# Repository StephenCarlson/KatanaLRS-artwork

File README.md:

KatanaLRS-artwork
=================

Hardware Files: Schematics and Layouts, Gerbers, PDFs

License
-------

This work is licensed under the Creative Commons Attribution-ShareAlike 3.0 Unported License. To view a copy of this license, visit <http://creativecommons.org/licenses/by-sa/3.0/> or send a letter to Creative Commons, 444 Castro Street, Suite 900, Mountain View, California, 94041, USA.

*Some portions of code may be subject to different licensing agreements.

THE SOFTWARE IS PROVIDED “AS IS”, WITHOUT WARRANTY OF ANY KIND, EXPRESS OR IMPLIED, INCLUDING BUT NOT LIMITED TO THE WARRANTIES OF MERCHANTABILITY, FITNESS FOR A PARTICULAR PURPOSE AND NONINFRINGEMENT. IN NO EVENT SHALL THE AUTHORS OR COPYRIGHT HOLDERS BE LIABLE FOR ANY CLAIM, DAMAGES OR OTHER LIABILITY, WHETHER IN AN ACTION OF CONTRACT, TORT OR OTHERWISE, ARISING FROM, OUT OF OR IN CONNECTION WITH THE SOFTWARE OR THE USE OR OTHER DEALINGS IN THE SOFTWARE.

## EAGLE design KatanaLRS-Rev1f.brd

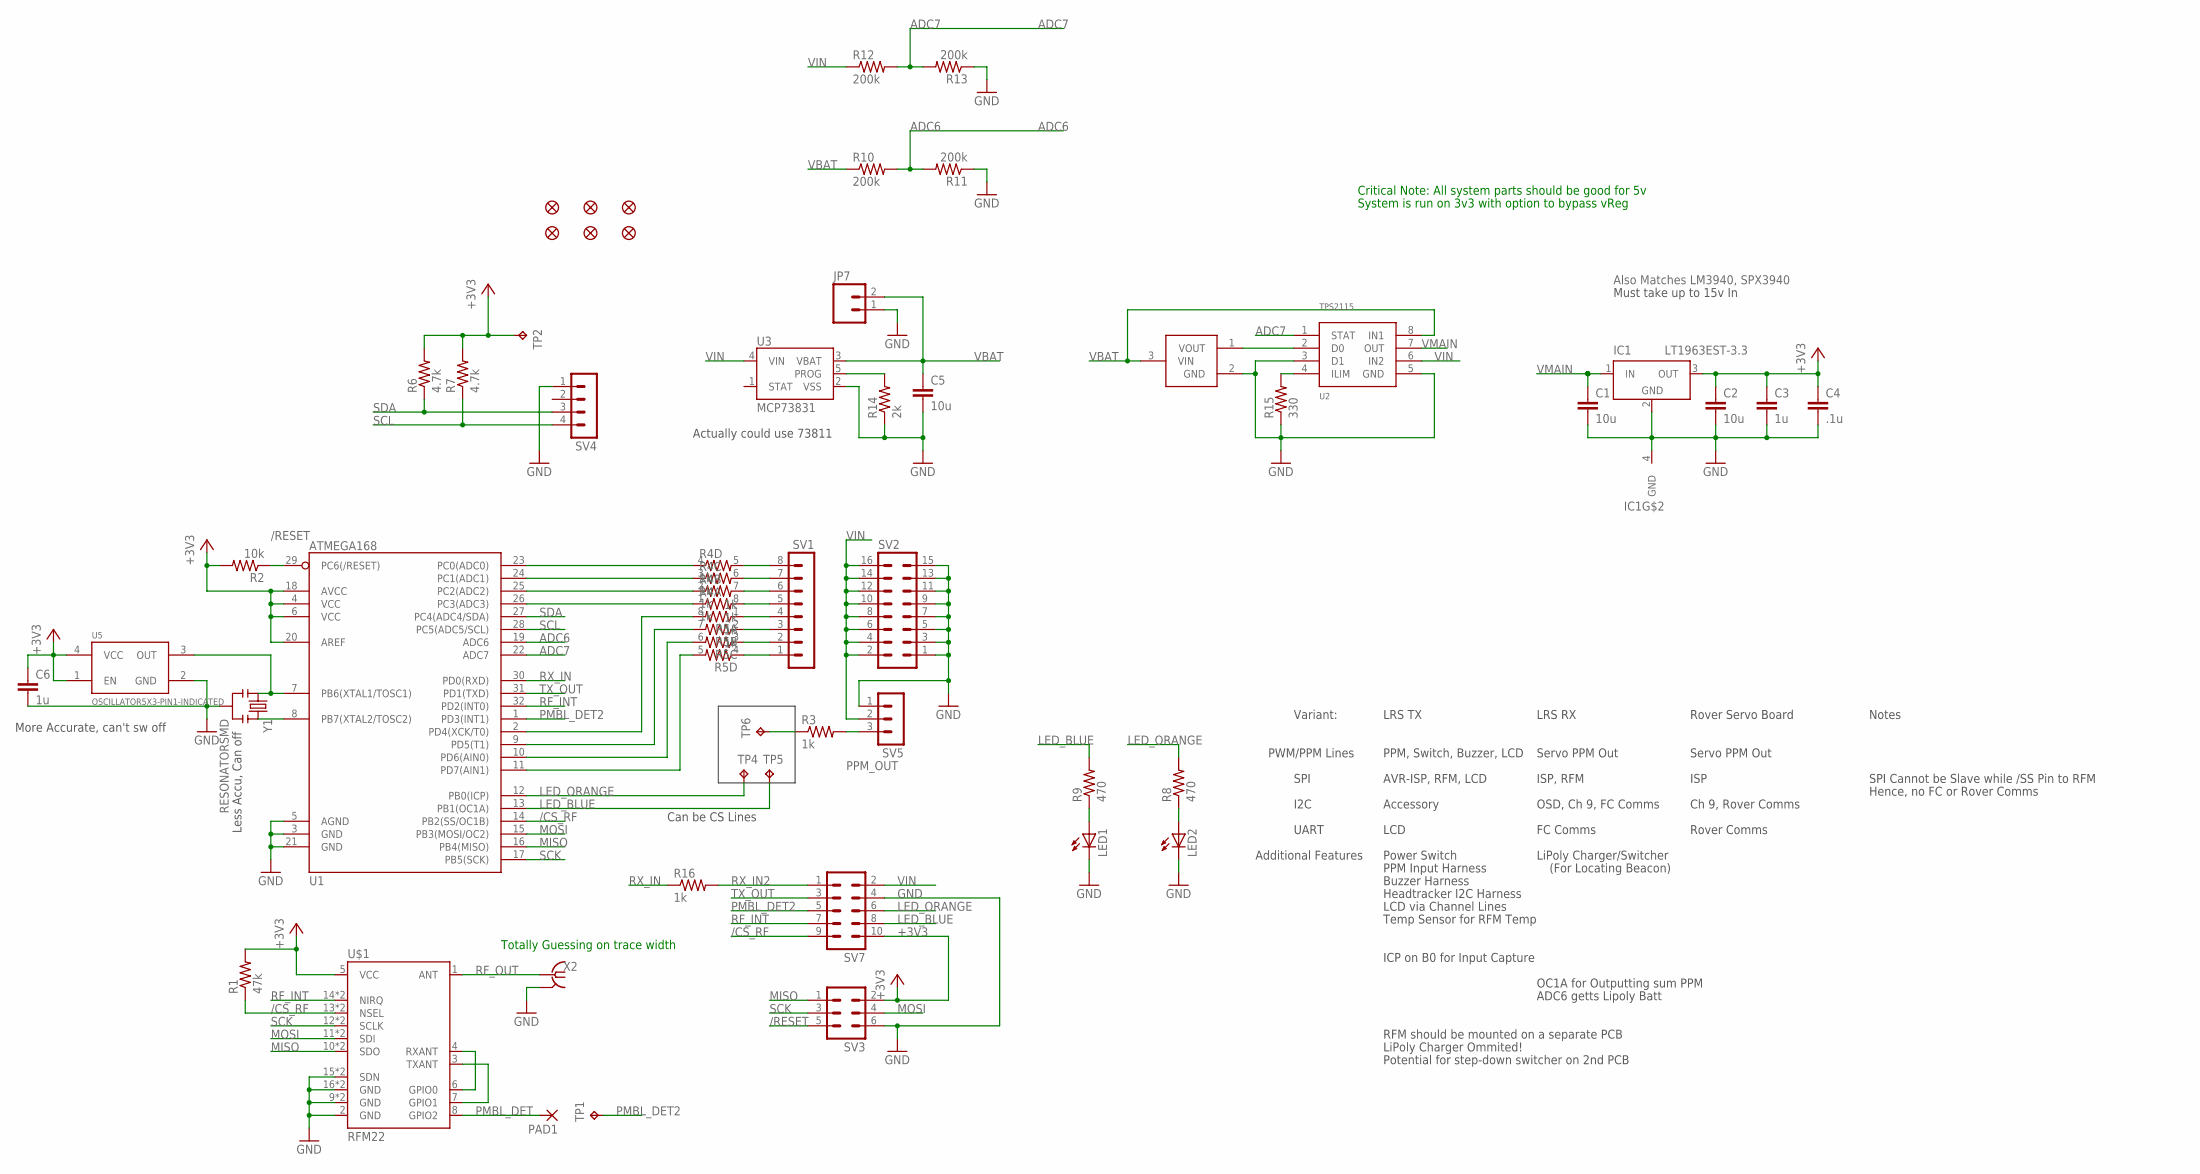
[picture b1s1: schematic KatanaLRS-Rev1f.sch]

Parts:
C1, C2, C5: 10u; 1206
C3: 1u; 0603-CAP
C4: .1u; 0603-CAP
C6: 1u; 0805
IC1: LT1963EST-3.3; SOT223
JP1, JP2, JP3, JP4, JP6, JP11: FIDUCIAL1X2; FIDUCIAL-1X2
JP7: M02JST-PTH-2; JST-2-PTH
LED1, LED2: LED1206; LED-1206
PAD1: SMD2; SMD1,27-2,54
R1: 47k; R0603
R2: 10k; R0603
R3, R16: 1k; R0603
R4, R5: 1k; 0603-ARV
R6, R7: 4.7k; R0603
R8, R9: 470; R0805
R10, R11, R12, R13: 200k; R0603
R14: 2k; R0603
R15: 330; R0603
SV1: MA08-1
SV2: MA08-2
SV3: MA03-2
SV4: MA04-1
SV5: MA03-1
SV7: MA05-2
TP1, TP2: TPTP15SQ; TP15SQ
TP4, TP5: TPTP07SQ; TP07SQ
TP6: TPTP10SQ; TP10SQ
U1: ATMEGA168; TQFP32-08
U2: TPS2115; TSSOP8
U3: MCP73831; SOT23-5
U5: OSCILLATOR5X3-PIN1-INDICATED; CRYSTAL-OSC-SMD-5X3
U$1: RFM22; RFM23B
U$4: TC54VC3002ECB713; SOT23-3
X2: Molex 073391-0060; BU-SMA-H
Y1: RESONATORSMD; RESONATOR-SMD

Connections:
+3V3: C2.1, C3.1, C4.1, C6.1, IC1.3 (OUT), R1.2, R2.2, R6.2, R7.2, SV3.2, SV7.10, TP2.TP, U1.4 (VCC), U1.6 (VCC), U1.18 (AVCC), U1.20 (AREF), U5.1 (EN), U5.4 (VCC), U$1.5 (VCC)
/CS_RF: R1.1, SV7.9, U1.14 (PB2(SS/OC1B)), U$1.13 (NSEL), U$1.13B (NSEL)
/RESET: R2.1, SV3.5, U1.29 (PC6(/RESET))
ADC6: R10.2, R11.2, U1.19 (ADC6)
ADC7: R12.2, R13.2, U1.22 (ADC7), U2.1 (STAT)
DP1: R5.7 (2), U1.9 (PD5(T1))
GND: C1.2, C2.2, C3.2, C4.2, C5.2, C6.2, IC1.2 (GND), IC1.4 (GND), JP7.1, LED1.C, LED2.C, R11.1, R13.1, R14.1, R15.1, SV2.1, SV2.3, SV2.5, SV2.7, SV2.9, SV2.11, SV2.13, SV2.15, SV3.6, SV4.1, SV5.1, SV7.4, U1.3 (GND), U1.5 (AGND), U1.21 (GND), U2.3 (D1), U2.5 (GND), U3.2 (VSS), U5.2 (GND), U$1.2 (GND), U$1.9 (GND), U$1.9B (GND), U$1.15 (SDN), U$1.15B (SDN), U$1.16 (GND), U$1.16B (GND), U$4.2 (GND), X2.2 (GND), X2.3 (GND), X2.4 (GND), X2.5 (GND), Y1.2
LED_BLUE: R9.2, SV7.8, TP5.TP, U1.13 (PB1(OC1A))
LED_ORANGE: R8.2, SV7.6, TP4.TP, U1.12 (PB0(ICP))
MISO: SV3.1, U1.16 (PB4(MISO)), U$1.10 (SDO), U$1.10B (SDO)
MOSI: SV3.4, U1.15 (PB3(MOSI/OC2)), U$1.11 (SDI), U$1.11B (SDI)
unnamed: R4.4 (1), U1.23 (PC0(ADC0))
unnamed: R4.3 (1), U1.24 (PC1(ADC1))
unnamed: U1.8 (PB7(XTAL2/TOSC2)), Y1.3
unnamed: U1.7 (PB6(XTAL1/TOSC1)), U5.3 (OUT), Y1.1
unnamed: R4.2 (1), U1.25 (PC2(ADC2))
unnamed: R15.2, U2.4 (ILIM)
unnamed: R4.1, U1.26 (PC3(ADC3))
unnamed: U$1.4 (RXANT), U$1.6 (GPIO0)
unnamed: LED1.A, R9.1
unnamed: R4.8 (2), SV1.5
unnamed: R4.7 (2), SV1.6
unnamed: R4.6 (2), SV1.7
unnamed: R4.5 (2), SV1.8
unnamed: U$1.3 (TXANT), U$1.7 (GPIO1)
unnamed: R5.4 (1), SV1.1
unnamed: R5.6 (2), U1.10 (PD6(AIN0))
unnamed: R5.3 (1), SV1.2
unnamed: R5.5 (2), U1.11 (PD7(AIN1))
unnamed: R5.8 (2), U1.2 (PD4(XCK/T0))
unnamed: U2.2 (D0), U$4.1 (VOUT)
unnamed: LED2.A, R8.1
unnamed: R3.1, TP6.TP
unnamed: R5.2 (1), SV1.3
unnamed: R5.1, SV1.4
unnamed: R14.2, U3.5 (PROG)
PMBL_DET: PAD1.1, U$1.8 (GPIO2)
PMBL_DET2: SV7.5, TP1.TP, U1.1 (PD3(INT1))
PPM_OUT: R3.2, SV5.3
RF_INT: SV7.7, U1.32 (PD2(INT0)), U$1.14 (NIRQ), U$1.14B (NIRQ)
RF_OUT: U$1.1 (ANT), X2.1
RX_IN: R16.1, U1.30 (PD0(RXD))
RX_IN2: R16.2, SV7.1
SCK: SV3.3, U1.17 (PB5(SCK)), U$1.12 (SCLK), U$1.12B (SCLK)
SCL: R7.1, SV4.4, U1.28 (PC5(ADC5/SCL))
SDA: R6.1, SV4.3, U1.27 (PC4(ADC4/SDA))
TX_OUT: SV7.3, U1.31 (PD1(TXD))
VBAT: C5.1, JP7.2, R10.1, U2.8 (IN1), U3.3 (VBAT), U$4.3 (VIN)
VIN: R12.1, SV2.2, SV2.4, SV2.6, SV2.8, SV2.10, SV2.12, SV2.14, SV2.16, SV5.2, SV7.2, U2.6 (IN2), U3.4 (VIN)
VMAIN: C1.1, IC1.1 (IN), U2.7 (OUT)

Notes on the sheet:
Variant:
PWM/PPM Lines
LRS TX
LRS RX
Rover Servo Board
PPM, Switch, Buzzer, LCD
Servo PPM Out
SPI
AVR-ISP, RFM, LCD
ISP, RFM
ISP
I2C
Accessory
OSD, Ch 9, FC Comms
Ch 9, Rover Comms
UART
LCD
FC Comms
Rover Comms
Additional Features
LiPoly Charger/Switcher
(For Locating Beacon)
Notes
SPI Cannot be Slave while /SS Pin to RFM
Hence, no FC or Rover Comms
Can be CS Lines
Power Switch
PPM Input Harness
Buzzer Harness
Headtracker I2C Harness
LCD via Channel Lines
Temp Sensor for RFM Temp
ICP on B0 for Input Capture
OC1A for Outputting sum PPM
Critical Note: All system parts should be good for 5v
System is run on 3v3 with option to bypass vReg
ADC6 getts Lipoly Batt
RFM should be mounted on a separate PCB
Totally Guessing on trace width
More Accurate, can't sw off

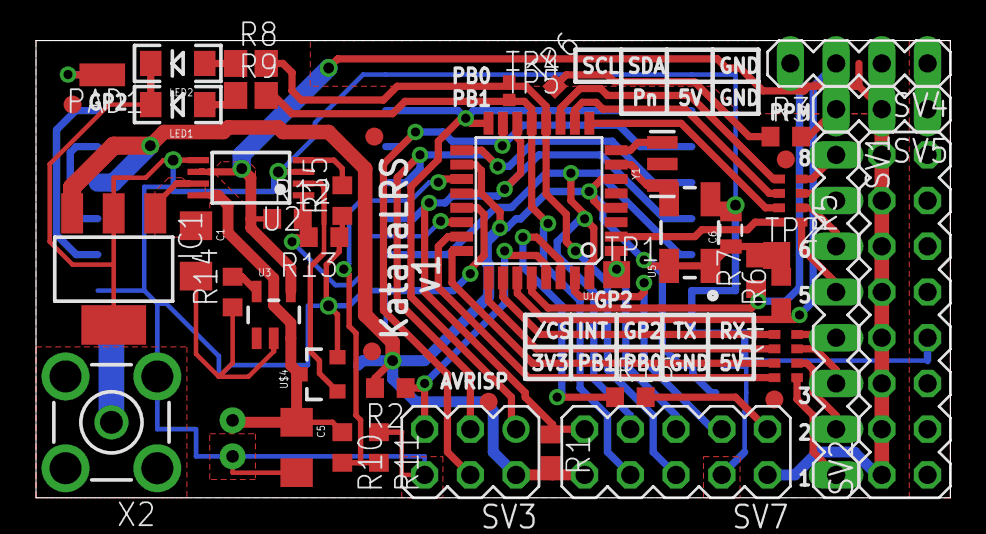
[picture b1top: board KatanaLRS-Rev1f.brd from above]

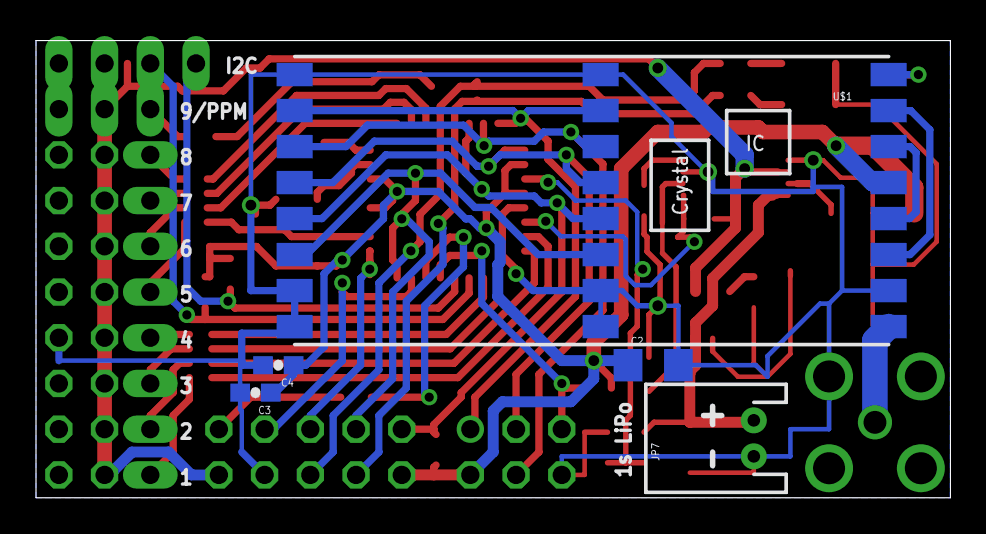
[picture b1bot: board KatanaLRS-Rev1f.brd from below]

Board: 2 copper layers, 50.8 x 25.4 mm, 52 parts (5 on the bottom side), 50 nets.

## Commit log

2014-03-06 Initial Commit of KatanaLRS Source Artwork
    Rev1F is the production version, Rev1G is corrections and realized/actual values used in populating the board.
    If I go for a Rev2, that will be added.
2014-03-18 Update README.md
    Copied the OpenROV License Statement for artwork
2014-03-18 Update LICENSE
    Annoying, no ability to redo License

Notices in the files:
parts and their libraries:
SparkFun: Licensing: CC v3.0 Share-Alike You are welcome to use this library for commercial purposes.
